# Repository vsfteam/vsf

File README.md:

# VSF -- Versaloon Software Framework

[中文](README_zh.md) |

Full name of VSF is "Versaloon Software Framework". VSF is an open-source software framework for embedded applications based on Apache2 license. VSF includes hal, a pre-emptive multi-thread kernel, services and components. VSF is implemented by C language with object-oriented programming methods(PLOOC).

## Overall Framework

## Catalogue
| Name               | Description                                               |
| ------------------ | --------------------------------------------------------- |
| document           | document                                                  |
| doxygen            | configuration of doxygen                                  |
| example            | demo codes                                                |
| hardware           | hardware of VSF development boards                        |
| patch              | some patches(for 3rd-party components, etc)               |
| script             |                                                           |
|  &emsp;cmake       | cmake scripts                                             |
| source             | source code of VSF                                        |
|  &emsp;component   | component(filesystem, stacks, UI, drivers, etc)           |
|  &emsp;hal         | hardware abstraction layer(ARCH support, chip drivers)    |
|  &emsp;kernel      | VSF pre-emptive/collaborative kernel                      |
|  &emsp;osa_service | software services based on kernel                         |
|  &emsp;service     | software services                                         |
|  &emsp;shell       | shell to use application software for other systems      |
|  &emsp;utilities   | base software utilities(preprocessor, compiler, list, etc)|

## Kernel
Pre-emptive kernel based on event-driven architecture, supporting mcs51, 8bit MCU, 32/64 bit ARM, riscv, x86, etc.

- event-driven architecture, sleep if no event occurred, lower-power naturally
- in pre-emptive mode, task switch is implemented by hardware swi(software interrupt), priority of task is the priority of the swi.
- pre-emptive scheduling for tasks with different priority, collaborative scheduling for tasks with the same priority
- can run in other RTOS as a task, or as swi ISR
- different tasks
  - event handler task -- minimum resources usage, 20 bytes ram usage for minimum configuration, 40 bytes ram usage for normal configuration
  - pt task
  - thread with dedicated stack -- depending on setjmp in libc
  - fsm task
  - other tasks in shell, eg pthread
- IPC: semaphore, mutex, trigger, queue, etc

## Components
- Reasonable framework for code re-use
- declarative development model
- standard interface, standard port for 3rd-party components
- software components
  - distbus -- distributed bus framework
  - fifo
  - heap
  - json
  - pool
  - stream
  - trace
- Components
  - fs -- filesystem with vfs support
  - input -- input sub-system
  - mal -- memory abstraction layer(normally known as 'block' device)
  - scsi -- SCSI device
  - tcpip -- TCPIP stack and netdrv drivers
  - ui -- UI and display drivers
  - usb -- USB host/slave stacks
  - bt -- bt stack(using btstack)

## HAL -- hardware abstraction layer
- standard hal interface and API -- eg: vsf_spi_init can be used with hardware SPI, GPIO emulated SPI, SPI from external usb device, etc
- IP core driver -- simplify porting by implement clock, reset, interrupt functions which is not provided by IP core
- template for different interfaces and functionalities
- interfaces
  - PM
  - GPIO
  - SPI
  - I2C
  - PWM
  - ADC
  - SWI
  - USART
  - FLASH
  - USB
  - ethernet

## Shell
To use applications from other system, shell can be used.

- SDL -- use applications based on SDL directly
- linux -- use applications based on linux directly
  - posix
  - devfs
  - socket
  - console
  - libraries
    - libusb
    - libgen
    - libsdl2
    - libcurl
    - etc

## 3rd-party
| Software          | Path                                                          | License    | Link                                               |
|-------------------|---------------------------------------------------------------|------------|----------------------------------------------------|
| btstack           | source/component/3rd-party/btstack/raw                        | Other      | https://github.com/bluekitchen/btstack             |
| coremark          | source/component/3rd-party/coremark/raw                       | Apache     | https://github.com/eembc/coremark                  |
| freetype          | source/component/3rd-party/freetype/raw                       | FreeType   | https://freetype.org/                              |
| zlib              | source/component/3rd-party/zlib/raw                           | zlib       | http://zlib.net/                                   |
| nuklear           | source/component/3rd-party/nuklear/raw                        | MTI        | https://github.com/Immediate-Mode-UI/Nuklear       |
| nnom              | source/component/3rd-party/nnom/raw                           | Apache 2.0 | https://github.com/majianjia/nnom                  |
| lua               | source/component/3rd-party/lua/raw                            | MIT        | https://www.lua.org/                               |
| lwip              | source/component/3rd-party/lwip/raw                           | BSD        | https://savannah.nongnu.org/projects/lwip/         |
| libpng            | source/component/3rd-party/libpng/raw                         | PNG2       | https://libpng.sf.net                              |
| libjpeg-turbo     | source/component/3rd-party/libjpeg-turbo/raw                  | BSD        | https://libjpeg-turbo.org/                         |
| SDL_ttf           | source/shell/media/sdl2/3rd-party/SDL_ttf                     | zlib       | https://hg.libsdl.org/SDL_ttf/                     |
| SDL_image         | source/shell/media/sdl2/3rd-party/SDL_image                   | zlib       | https://hg.libsdl.org/SDL_image/                   |
| lvgl              | source/component/3rd-party/lvgl/raw/lvgl                      | MIT        | https://lvgl.io/                                   |
| lv_lib_freetype   | source/component/3rd-party/lvgl/extension/lv_lib_freetype/raw | MIT        | https://lvgl.io/                                   |
| CMSIS             | source/utilities/compiler/arm/3rd-party/CMSIS                 | Apache 2.0 | https://github.com/ARM-software/CMSIS_5            |
| PLOOC             | source/utilities/3rd-party/PLOOC/raw                          | Apache 2.0 | https://github.com/GorgonMeducer/PLOOC             |
| mbedtls           | source/component/3rd-party/mbedtls/raw                        | Apache 2.0 | https://tls.mbed.org/                              |
| Segger_RTT        | source/component/3rd-party/segger/raw/RTT                     | segger     | https://wiki.segger.com/RTT                        |
| Segger_SystemView | source/component/3rd-party/segger/raw/SystemView              | segger     | https://wiki.segger.com/SystemView                 |
| nuconsole         | source/component/3rd-party/nuconsole/raw                      | nuvoton    | https://www.nuvoton.com.cn/                        |
| AIC8800M_SDK      | source/hal/driver/AIC/AIC8800/vendor                          | aic        | http://www.aicsemi.com/                            |
| awtk              |                                                               | LGPL 2.1   | https://www.zlg.cn/index/pub/awtk.html             |
| littlefs          | source/component/3rd-party/littlefs/raw                       | BSD        | https://github.com/littlefs-project/littlefs       |
| getopt_long       | source/shell/sys/linux/lib/3rd-party/getopt                   | OpenBSD    | https://github.com/openbsd/src                     |
| regex             | source/shell/sys/linux/lib/3rd-party/regex                    | OpenBSD    | https://github.com/openbsd/src                     |
| fnmatch           | source/shell/sys/linux/lib/3rd-party/fnmatch                  | BSD        | http://www.jbox.dk/sanos/source/lib/fnmatch.c.html |
| glob              | source/shell/sys/linux/lib/3rd-party/glob                     | BSD        | https://github.com/cloudius-systems/musl           |
| setjmp            | source/hal/arch/x86/win                                       | BSD        |                                                    |
| libtuv            | source/shell/sys/linux/lib/3rd-party/libtuv/raw               | Apache 2.0 | https://github.com/Samsung/libtuv                  |
| scgui             | source/component/ui/tgui/view/scgui_view/scgui.c&h            | MIT        | https://gitee.com/li_yucheng/scgui                 |

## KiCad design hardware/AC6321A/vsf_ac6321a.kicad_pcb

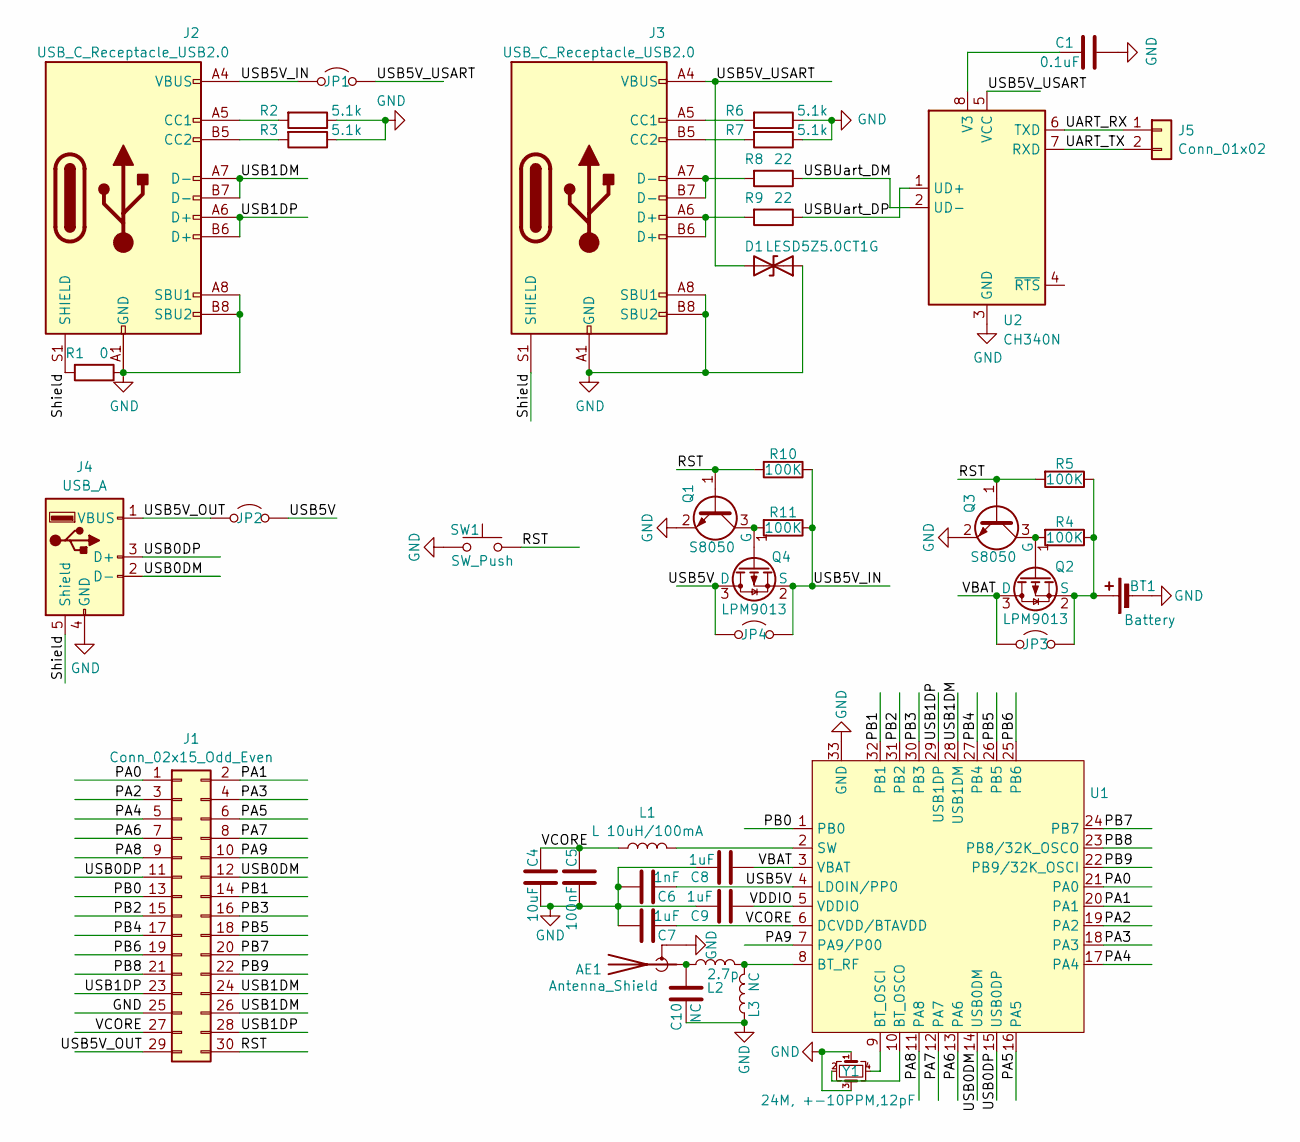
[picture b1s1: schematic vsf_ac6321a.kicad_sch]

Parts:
AE1: Antenna_Shield; Texas_SWRA117D_2.4GHz_Right
BT1: Battery; PinHeader_1x02_P2.54mm_Vertical
C1: 0.1uF; C_0402_1005Metric
C4: 10uF; C_0402_1005Metric
C5: 100nF; C_0402_1005Metric
C6: 1nF; C_0402_1005Metric
C7, C8, C9: 1uF; C_0402_1005Metric
C10: NC; C_0402_1005Metric
D1: LESD5Z5.0CT1G; D_SOD-523
J1: Conn_02x15_Odd_Even; PinHeader_2x15_P2.54mm_Horizontal
J2, J3: USB_C_Receptacle_USB2.0; USB_C_Receptacle_Palconn_UTC16-G_DOWN1.6
J4: USB_A; USB-A-8.5_DOWN3.4
J5: Conn_01x02; PinHeader_1x02_P2.54mm_Vertical
JP1, JP2, JP3, JP4: Jumper_2_Open; SolderJumper-2_P0.8mm_Open_Pad0.6x0.8mm
L1: L 10uH/100mA; L_0603_1608Metric
L2: 2.7p; L_0603_1608Metric
L3: NC; L_0603_1608Metric
Q1, Q3: S8050; TSOT-23
Q2, Q4: LPM9013; SOT-23
R1: 0; R_0402_1005Metric
R2, R3, R6, R7: 5.1k; R_0402_1005Metric
R4, R5, R10, R11: 100K; R_0402_1005Metric
R8, R9: 22; R_0402_1005Metric
SW1: SW_Push; JHA004
U1: QFN-32-1EP_4x4mm_P0.4mm_EP2.65x2.65mm
U2: CH340N; SOP-8_3.9x4.9mm_P1.27mm
Y1: 24M, +-10PPM,12pF; Oscillator_SMD_Abracon_ASE-4Pin_3.2x2.5mm

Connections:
/PA0: J1.1, U1.21 (PA0)
/PA1: J1.2, U1.20 (PA1)
/PA2: J1.3, U1.19 (PA2)
/PA3: J1.4, U1.18 (PA3)
/PA4: J1.5, U1.17 (PA4)
/PA5: J1.6, U1.16 (PA5)
/PA6: J1.7, U1.13 (PA6)
/PA7: J1.8, U1.12 (PA7)
/PA8: J1.9, U1.11 (PA8)
/PA9: J1.10, U1.7 (PA9/P00)
/PB0: J1.13, U1.1 (PB0)
/PB1: J1.14, U1.32 (PB1)
/PB2: J1.15, U1.31 (PB2)
/PB3: J1.16, U1.30 (PB3)
/PB4: J1.17, U1.27 (PB4)
/PB5: J1.18, U1.26 (PB5)
/PB6: J1.19, U1.25 (PB6)
/PB7: J1.20, U1.24 (PB7)
/PB8: J1.21, U1.23 (PB8/32K_OSCO)
/PB9: J1.22, U1.22 (PB9/32K_OSCI)
/RST: J1.30, Q1.1 (B), Q3.1 (B), R5.2, R10.2, SW1.2
/Shield: J2.S1 (SHIELD), J3.S1 (SHIELD), J4.5 (Shield), R1.2
/UART_RX: J5.1, U2.6 (TXD)
/UART_TX: J5.2, U2.7 (RXD)
/USB0DM: J1.12, J4.2 (D-), U1.14 (USB0DM)
/USB0DP: J1.11, J4.3 (D+), U1.15 (USB0DP)
/USB1DM: J1.24, J1.26, J2.A7 (D-), J2.B7 (D-), U1.28 (USB1DM)
/USB1DP: J1.23, J1.28, J2.A6 (D+), J2.B6 (D+), U1.29 (USB1DP)
/USB5V: C6.2, JP2.2 (B), JP4.1 (A), Q4.3 (D), U1.4 (LDOIN/PP0)
/USB5V_IN: J2.A4 (VBUS), J2.A9 (VBUS), J2.B4 (VBUS), J2.B9 (VBUS), JP1.1 (A), JP4.2 (B), Q4.2 (S), R10.1, R11.1
/USB5V_OUT: J1.29, J4.1 (VBUS), JP2.1 (A)
/USB5V_USART: D1.2 (A2), J3.A4 (VBUS), J3.A9 (VBUS), J3.B4 (VBUS), J3.B9 (VBUS), JP1.2 (B), U2.5 (VCC)
/USBUart_DM: R8.1, U2.2 (UD-)
/USBUart_DP: R9.1, U2.1 (UD+)
/VBAT: C8.2, JP3.1 (A), Q2.3 (D), U1.3 (VBAT)
/VCORE: C4.2, C5.2, C7.2, J1.27, L1.1, U1.6 (DCVDD/BTAVDD)
/VDDIO: C9.2, U1.5 (VDDIO)
GND: AE1.2 (Shield), BT1.2 (-), C1.2, C4.1, C5.1, C6.1, C7.1, C8.1, C9.1, C10.1, D1.1 (A1), J1.25, J2.A1 (GND), J2.A8 (SBU1), J2.A12 (GND), J2.B1 (GND), J2.B8 (SBU2), J2.B12 (GND), J3.A1 (GND), J3.A8 (SBU1), J3.A12 (GND), J3.B1 (GND), J3.B8 (SBU2), J3.B12 (GND), J4.4 (GND), L3.1, Q1.2 (E), Q3.2 (E), R1.1, R2.1, R3.1, R6.1, R7.1, SW1.1, U1.33 (GND), U2.3 (GND), Y1.1, Y1.3
unnamed: AE1.1 (A), C10.2, L2.1
unnamed: BT1.1 (+), JP3.2 (B), Q2.2 (S), R4.1, R5.1
unnamed: J2.A5 (CC1), R2.2
unnamed: J2.B5 (CC2), R3.2
unnamed: J3.A5 (CC1), R6.2
unnamed: J3.B5 (CC2), R7.2
unnamed: J3.A6 (D+), J3.B6 (D+), R9.2
unnamed: J3.A7 (D-), J3.B7 (D-), R8.2
unnamed: Q1.3 (C), Q4.1 (G), R11.2
unnamed: Q2.1 (G), Q3.3 (C), R4.2
unnamed: U1.9 (BT_OSCI), Y1.4
unnamed: U1.10 (BT_OSCO), Y1.2
unnamed: L2.2, L3.2, U1.8 (BT_RF)
unnamed: L1.2, U1.2 (SW)
unnamed: C1.1, U2.8 (V3)

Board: 2 copper layers, 42 parts (0 on the bottom side), 53 nets, no tracks yet.

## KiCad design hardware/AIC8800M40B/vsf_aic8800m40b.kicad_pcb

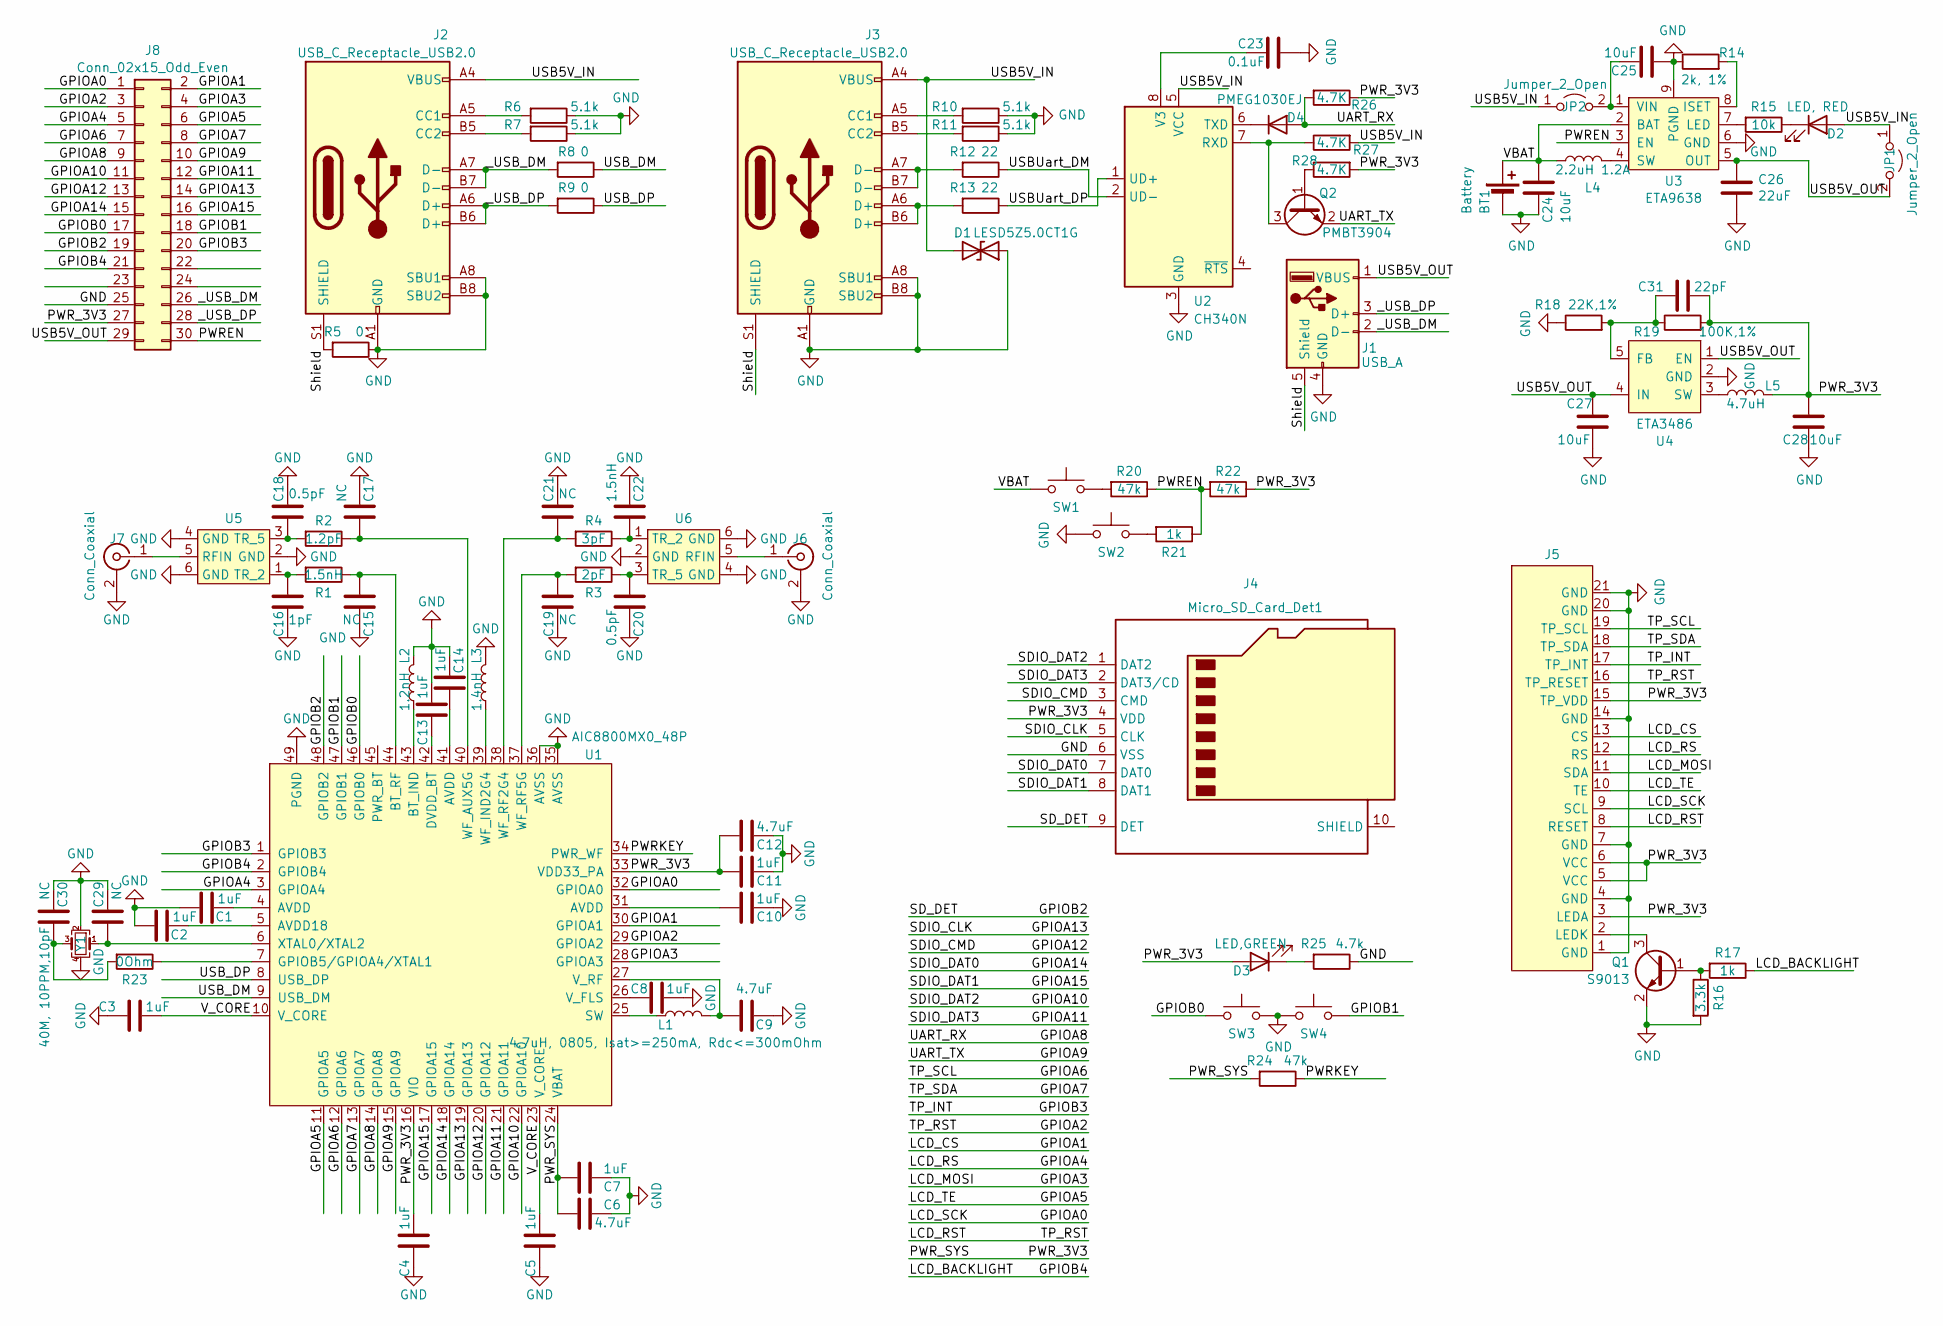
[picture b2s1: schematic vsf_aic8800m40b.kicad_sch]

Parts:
BT1: Battery; PinHeader_1x02_P2.54mm_Vertical
C1, C2, C3, C4, C5, C7, C8, C10, C11, C13, C14: 1uF; C_0402_1005Metric
C6, C9, C12: 4.7uF; C_0402_1005Metric
C15, C17, C19, C21, C29, C30: NC; C_0402_1005Metric
C16: 1pF; C_0402_1005Metric
C18, C20: 0.5pF; C_0402_1005Metric
C22: 1.5nH; C_0402_1005Metric
C23: 0.1uF; C_0402_1005Metric
C24, C25: 10uF; C_1206_3216Metric
C26: 22uF; C_1206_3216Metric
C27, C28: 10uF; C_0805_2012Metric
C31: 22pF; C_0402_1005Metric
D1: LESD5Z5.0CT1G; D_SOD-523
D2: LED, RED; LED_0603_1608Metric
D3: LED,GREEN; LED_0603_1608Metric
D4: PMEG1030EJ; D_SOD-323
J1: USB_A; USB-A-8.5_DOWN3.4
J2, J3: USB_C_Receptacle_USB2.0; USB_C_Receptacle_Palconn_UTC16-G_DOWN1.6
J4: Micro_SD_Card_Det1; MicroSD_Tiny
J5: Molex_502250-2191_2Rows-21Pins-1MP_P0.60mm_Horizontal
J6, J7: Conn_Coaxial; U.FL_Molex_MCRF_73412-0110_Vertical
J8: Conn_02x15_Odd_Even; PinHeader_2x15_P2.54mm_Horizontal
JP1, JP2: Jumper_2_Open; SolderJumper-2_P0.8mm_Open_Pad0.6x0.8mm
L1: 4.7uH, 0805, Isat>=250mA, Rdc<=300mOhm; L_0805_2012Metric
L2: 1.2nH; L_0402_1005Metric
L3: 1.4nH; L_0402_1005Metric
L4: 2.2uH 1.2A; L_1210_3225Metric
L5: 4.7uH; L_1210_3225Metric
Q1: S9013; SOT-23
Q2: PMBT3904; SOT-23
R1: 1.5nH; R_0402_1005Metric
R2: 1.2pF; R_0402_1005Metric
R3: 2pF; R_0402_1005Metric
R4: 3pF; R_0402_1005Metric
R5, R8, R9: 0; R_0402_1005Metric
R6, R7, R10, R11: 5.1k; R_0402_1005Metric
R12, R13: 22; R_0402_1005Metric
R14: 2k, 1%; R_0402_1005Metric
R15: 10k; R_0402_1005Metric
R16: 3.3k; R_0402_1005Metric
R17, R21: 1k; R_0402_1005Metric
R18: 22K,1%; R_0402_1005Metric
R19: 100K,1%; R_0402_1005Metric
R20, R22, R24: 47k; R_0402_1005Metric
R23: 0Ohm; R_0402_1005Metric
R25: 4.7k; R_0402_1005Metric
R26, R27, R28: 4.7K; R_0402_1005Metric
SW1, SW2, SW3, SW4: SW_Push; JHA004
U1: AIC8800MX0_48P; QFN-48.10.14.10.14-1EP_5x5mm_P0.35mm_EP3.7x3.7mm_ThermalVias
U2: CH340N; SOP-8_3.9x4.9mm_P1.27mm
U3: ETA9638; HSOP-8-1EP_3.9x4.9mm_P1.27mm_EP2.41x3.1mm_ThermalVias
U4: ETA3486; SOT-23-5
U5, U6: Filter_SLFD18-5R950G-07T
Y1: 40M, 10PPM,10pF; Oscillator_SMD_Abracon_ASE-4Pin_3.2x2.5mm

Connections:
/GPIOA0: J5.9 (SCL), J8.1, U1.32 (GPIOA0)
/GPIOA1: J5.13 (CS), J8.2, U1.30 (GPIOA1)
/GPIOA2: J5.8 (RESET), J5.16 (TP_RESET), J8.3, U1.29 (GPIOA2)
/GPIOA3: J5.11 (SDA), J8.4, U1.28 (GPIOA3)
/GPIOA4: J5.12 (RS), J8.5, U1.3 (GPIOA4)
/GPIOA5: J5.10 (TE), J8.6, U1.11 (GPIOA5)
/GPIOA6: J5.19 (TP_SCL), J8.7, U1.12 (GPIOA6)
/GPIOA7: J5.18 (TP_SDA), J8.8, U1.13 (GPIOA7)
/GPIOA8: D4.2 (A), J8.9, R26.2, U1.14 (GPIOA8)
/GPIOA9: J8.10, Q2.2 (E), U1.15 (GPIOA9)
/GPIOA10: J4.1 (DAT2), J8.11, U1.22 (GPIOA10)
/GPIOA11: J4.2 (DAT3/CD), J8.12, U1.21 (GPIOA11)
/GPIOA12: J4.3 (CMD), J8.13, U1.20 (GPIOA12)
/GPIOA13: J4.5 (CLK), J8.14, U1.19 (GPIOA13)
/GPIOA14: J4.7 (DAT0), J8.15, U1.18 (GPIOA14)
/GPIOA15: J4.8 (DAT1), J8.16, U1.17 (GPIOA15)
/GPIOB0: J8.17, SW3.1, U1.46 (GPIOB0)
/GPIOB1: J8.18, SW4.2, U1.47 (GPIOB1)
/GPIOB2: J4.9 (DET), J8.19, U1.48 (GPIOB2)
/GPIOB3: J5.17 (TP_INT), J8.20, U1.1 (GPIOB3)
/GPIOB4: J8.21, R17.1, U1.2 (GPIOB4)
/PWREN: J8.30, R20.1, R21.1, R22.2, U3.3 (EN)
/PWRKEY: R24.1, U1.34 (PWR_WF)
/PWR_3V3: C4.1, C6.1, C7.1, C11.1, C12.1, C28.1, C31.2, D3.2 (A), J4.4 (VDD), J5.3 (LEDA), J5.5 (VCC), J5.6 (VCC), J5.15 (TP_VDD), J8.27, L5.2, R19.2, R22.1, R24.2, R26.1, R28.2, U1.16 (VIO), U1.24 (VBAT), U1.33 (VDD33_PA)
/Shield: J1.5 (Shield), J2.S1 (SHIELD), J3.S1 (SHIELD), R5.2
/USB5V_IN: D1.2 (A2), D2.2 (A), J2.A4 (VBUS), J2.A9 (VBUS), J2.B4 (VBUS), J2.B9 (VBUS), J3.A4 (VBUS), J3.A9 (VBUS), J3.B4 (VBUS), J3.B9 (VBUS), JP1.1 (A), JP2.1 (A), R27.2, U2.5 (VCC)
/USB5V_OUT: C26.1, C27.1, J1.1 (VBUS), J8.29, JP1.2 (B), U3.5 (OUT), U4.1 (EN), U4.4 (IN)
/USBUart_DM: R12.1, U2.2 (UD-)
/USBUart_DP: R13.1, U2.1 (UD+)
/USB_DM: R8.1, U1.9 (USB_DM)
/USB_DP: R9.1, U1.8 (USB_DP)
/VBAT: BT1.1 (+), C24.1, L4.1, SW1.1, U3.2 (BAT)
/V_CORE: C3.1, C5.1, U1.10 (V_CORE), U1.23 (V_CORE)
/_USB_DM: J1.2 (D-), J2.A7 (D-), J2.B7 (D-), J8.26, R8.2
/_USB_DP: J1.3 (D+), J2.A6 (D+), J2.B6 (D+), J8.28, R9.2
GND: BT1.2 (-), C1.2, C2.2, C3.2, C4.2, C5.2, C6.2, C7.2, C8.2, C9.1, C10.2, C11.2, C12.2, C13.1, C14.1, C15.2, C16.2, C17.1, C18.1, C19.2, C20.2, C21.1, C22.1, C23.2, C24.2, C25.2, C26.2, C27.2, C28.2, C29.1, C30.1, D1.1 (A1), J1.4 (GND), J2.A1 (GND), J2.A8 (SBU1), J2.A12 (GND), J2.B1 (GND), J2.B8 (SBU2), J2.B12 (GND), J3.A1 (GND), J3.A8 (SBU1), J3.A12 (GND), J3.B1 (GND), J3.B8 (SBU2), J3.B12 (GND), J4.6 (VSS), J5.1 (GND), J5.4 (GND), J5.7 (GND), J5.14 (GND), J5.20 (GND), J5.21 (GND), J6.2 (Ext), J7.2 (Ext), J8.25, L2.2, L3.2, Q1.2 (E), R5.1, R6.1, R7.1, R10.1, R11.1, R14.1, R16.2, R18.1, R25.1, SW2.1, SW3.2, SW4.1, U1.35 (AVSS), U1.36 (AVSS), U1.49 (PGND), U2.3 (GND), U3.6 (GND), U3.9 (PGND), U4.2 (GND), U5.2 (GND), U5.4 (GND), U5.6 (GND), U6.2 (GND), U6.4 (GND), U6.6 (GND), Y1.2, Y1.4
unnamed: C1.1, U1.4 (AVDD)
unnamed: C10.1, U1.31 (AVDD)
unnamed: C14.2, U1.41 (AVDD)
unnamed: C30.2, R23.2, Y1.3
unnamed: D2.1 (K), R15.1
unnamed: D3.1 (K), R25.2
unnamed: D4.1 (K), U2.6 (TXD)
unnamed: J2.A5 (CC1), R6.2
unnamed: J2.B5 (CC2), R7.2
unnamed: J3.A5 (CC1), R10.2
unnamed: J3.B5 (CC2), R11.2
unnamed: J3.A6 (D+), J3.B6 (D+), R13.2
unnamed: J3.A7 (D-), J3.B7 (D-), R12.2
unnamed: J5.2 (LEDK), Q1.3 (C)
unnamed: J6.1 (In), U6.5 (RFIN)
unnamed: J7.1 (In), U5.5 (RFIN)
unnamed: C25.1, JP2.2 (B), U3.1 (VIN)
unnamed: Q1.1 (B), R16.1, R17.2
unnamed: Q2.1 (B), R28.1
unnamed: Q2.3 (C), R27.1, U2.7 (RXD)
unnamed: R20.2, SW1.2
unnamed: R21.2, SW2.2
unnamed: C2.1, U1.5 (AVDD18)
unnamed: L2.1, U1.43 (BT_IND)
unnamed: C15.1, R1.1, U1.44 (BT_RF)
unnamed: C13.2, U1.42 (DVDD_BT)
unnamed: R23.1, U1.7 (GPIOB5/GPIOA4/XTAL1)
unnamed: L1.1, U1.25 (SW)
unnamed: C8.1, U1.26 (V_FLS)
unnamed: C9.2, L1.2, U1.27 (V_RF)
unnamed: C17.2, R2.1, U1.40 (WF_AUX5G)
unnamed: L3.1, U1.39 (WF_IND2G4)
unnamed: C21.2, R4.2, U1.38 (WF_RF2G4)
unnamed: C19.1, R3.2, U1.37 (WF_RF5G)
unnamed: C29.2, U1.6 (XTAL0/XTAL2), Y1.1
unnamed: C23.1, U2.8 (V3)
unnamed: R14.2, U3.8 (ISET)
unnamed: R15.2, U3.7 (LED)
unnamed: L4.2, U3.4 (SW)
unnamed: C31.1, R18.2, R19.1, U4.5 (FB)
unnamed: L5.1, U4.3 (SW)
unnamed: C16.1, R1.2, U5.1 (TR_2)
unnamed: C18.2, R2.2, U5.3 (TR_5)
unnamed: C22.2, R4.1, U6.1 (TR_2)
unnamed: C20.1, R3.1, U6.3 (TR_5)

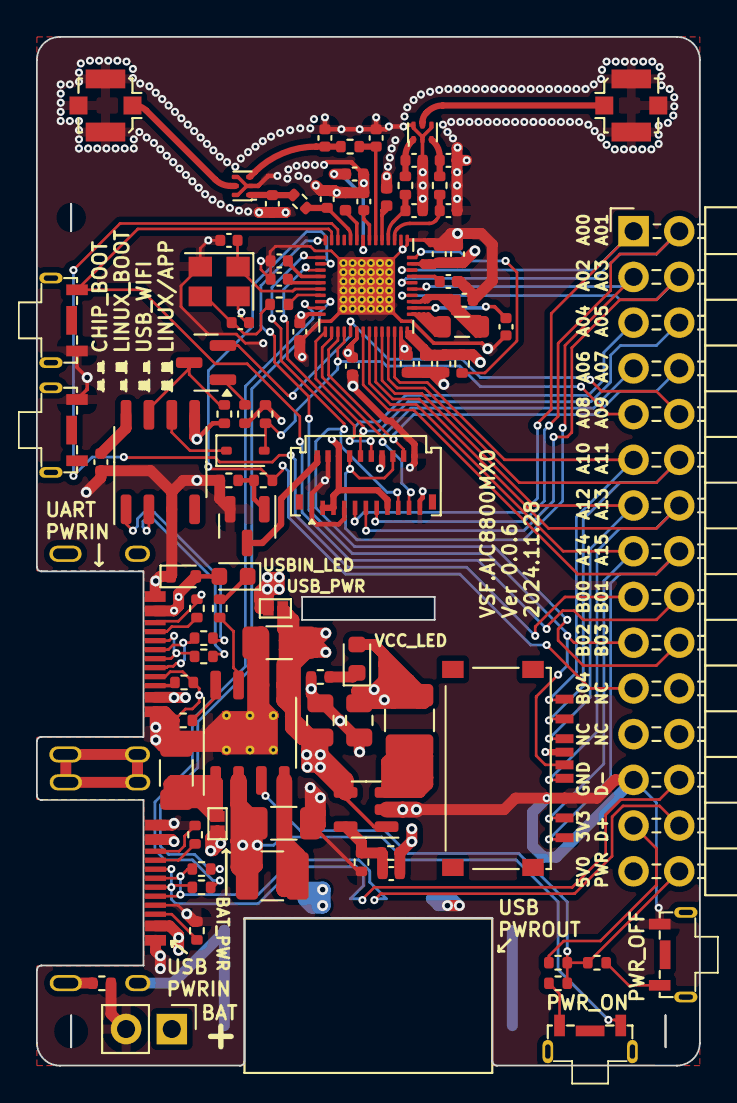
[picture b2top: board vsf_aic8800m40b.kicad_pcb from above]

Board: 4 copper layers, 36.8 x 57.2 mm, 92 parts (0 on the bottom side), 81 nets.

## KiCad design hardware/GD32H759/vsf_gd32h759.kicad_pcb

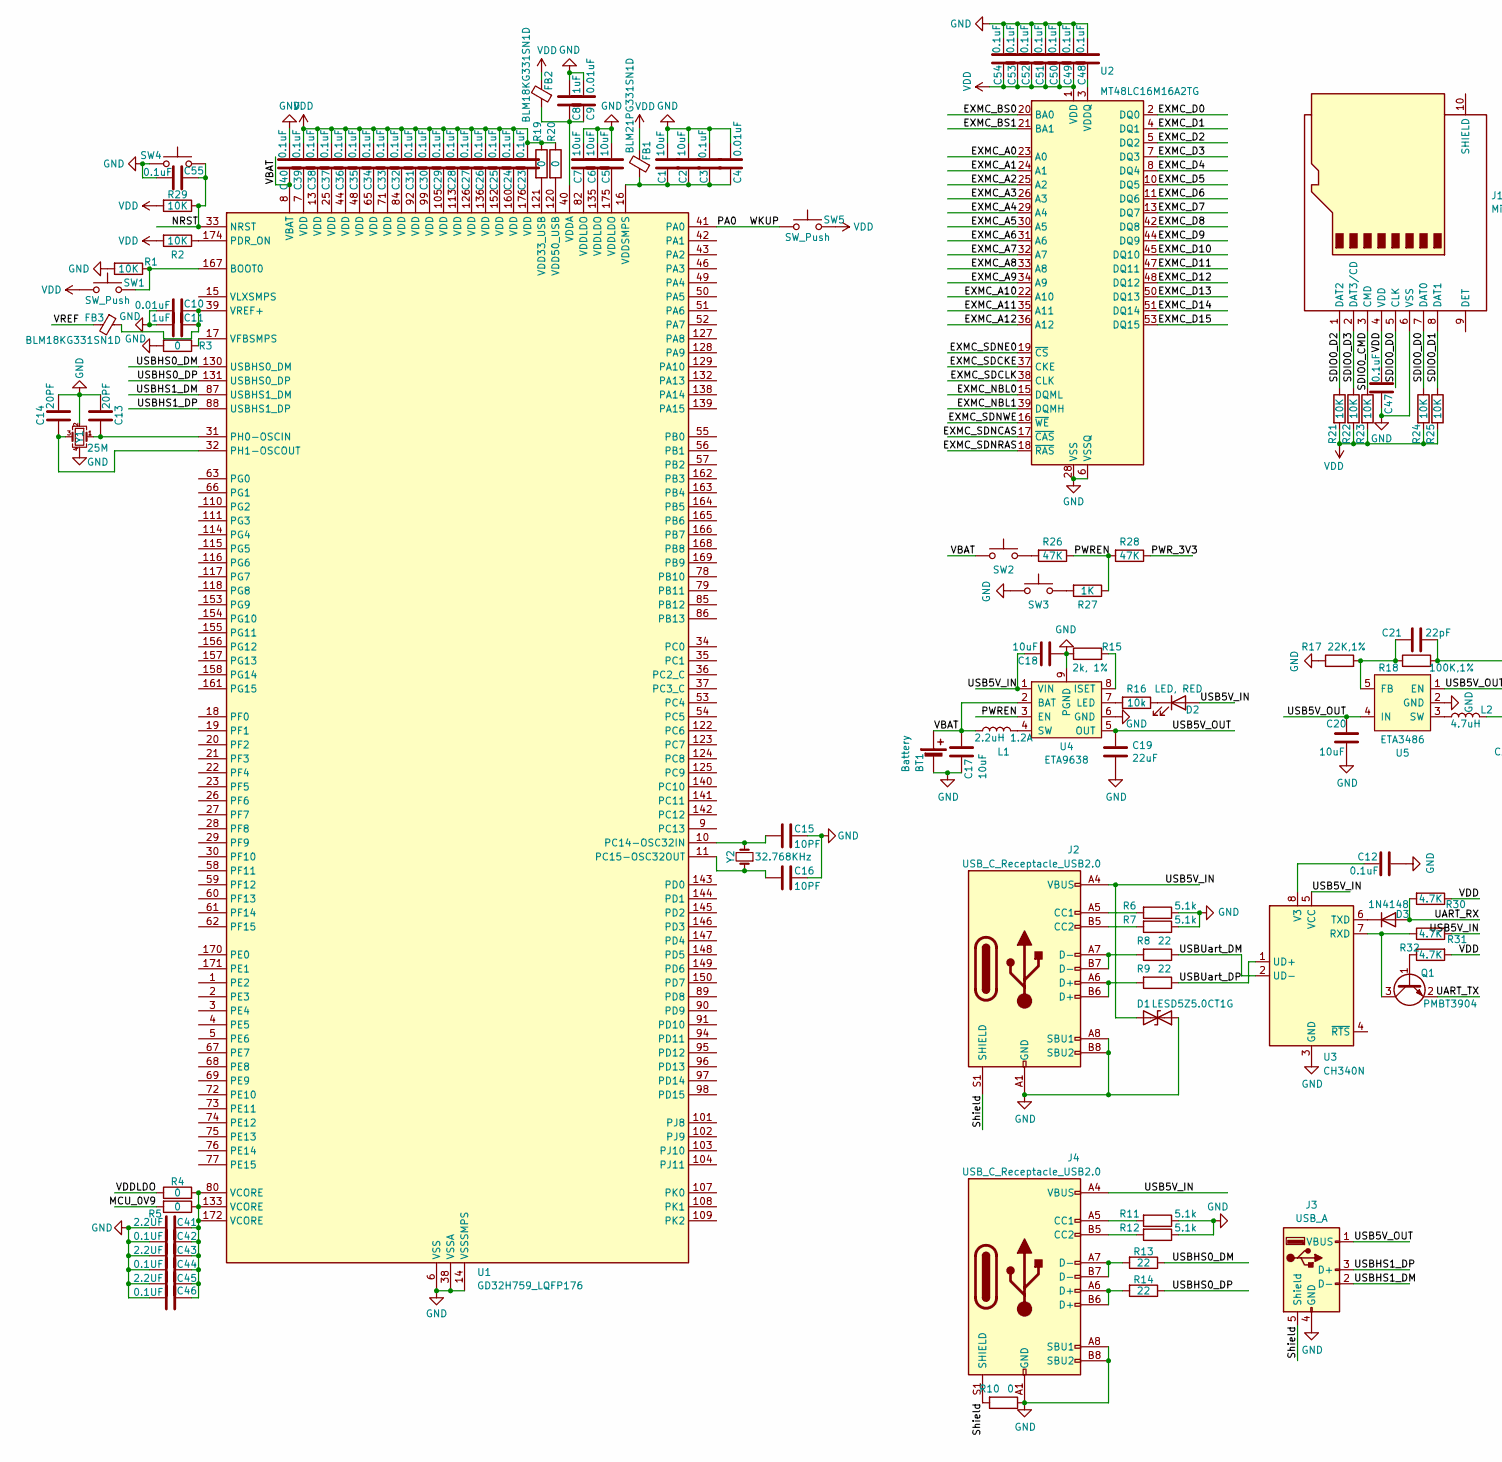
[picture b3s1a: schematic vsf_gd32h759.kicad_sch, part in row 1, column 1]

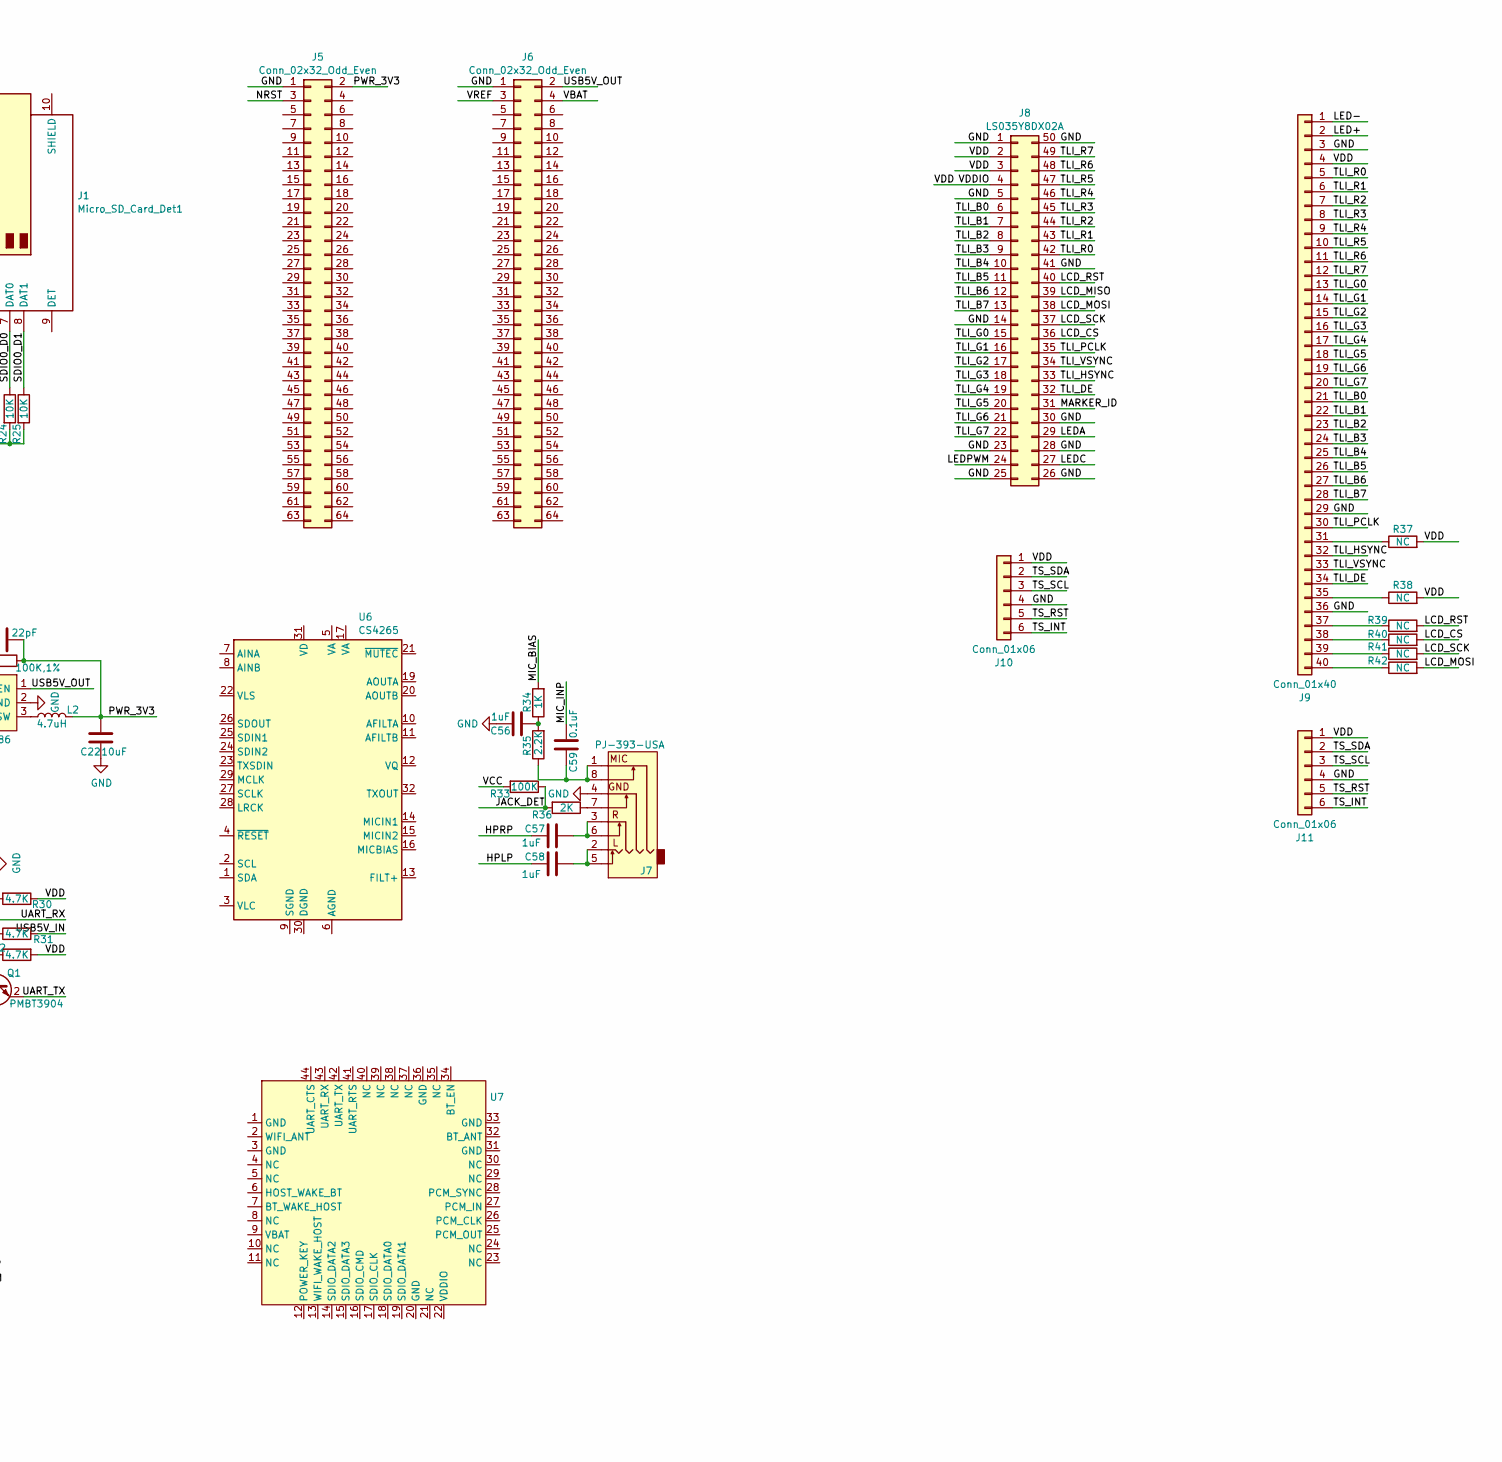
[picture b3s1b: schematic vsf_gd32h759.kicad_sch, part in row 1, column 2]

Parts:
BT1: Battery; PinHeader_1x02_P2.54mm_Vertical
C1, C2, C5, C6, C7: 10uF; C_0402_1005Metric
C3, C12, C23, C24, C25, C26, C27, C28, C29, C30, C31, C32, C33, C34, C35, C36, C37, C38, C39, C40, C47, C48, C49, C50, C51, C52, C53, C54, C55, C59: 0.1uF; C_0402_1005Metric
C4, C9, C10: 0.01uF; C_0402_1005Metric
C8, C11, C56, C57, C58: 1uF; C_0402_1005Metric
C13, C14: 20PF; C_0402_1005Metric
C15, C16: 10PF; C_0402_1005Metric
C17, C18: 10uF; C_1206_3216Metric
C19: 22uF; C_1206_3216Metric
C20, C22: 10uF; C_0805_2012Metric
C21: 22pF; C_0402_1005Metric
C41, C43, C45: 2.2UF; C_0402_1005Metric
C42, C44, C46: 0.1UF; C_0402_1005Metric
D1: LESD5Z5.0CT1G; D_SOD-523
D2: LED, RED; LED_0603_1608Metric
D3: 1N4148; D_SOD-523
FB1: BLM21PG331SN1D
FB2, FB3: BLM18KG331SN1D
J1: Micro_SD_Card_Det1
J2, J4: USB_C_Receptacle_USB2.0; USB_C_Receptacle_Palconn_UTC16-G_DOWN1.6
J3: USB_A; USB-A-8.5_DOWN3.4
J5, J6: Conn_02x32_Odd_Even; PinHeader_2x32_P2.54mm_Vertical
J7: PJ-393-USA; PJ-393
J8: LS035Y8DX02A
J9: Conn_01x40
J10, J11: Conn_01x06
L1: 2.2uH 1.2A; L_1210_3225Metric
L2: 4.7uH; L_1210_3225Metric
Q1: PMBT3904; SOT-23
R1, R2, R21, R22, R23, R24, R25, R29: 10K; R_0402_1005Metric
R3, R4, R5, R10, R19, R20: 0; R_0402_1005Metric
R6, R7, R11, R12: 5.1k; R_0402_1005Metric
R8, R9, R13, R14: 22; R_0402_1005Metric
R15: 2k, 1%; R_0402_1005Metric
R16: 10k; R_0402_1005Metric
R17: 22K,1%; R_0402_1005Metric
R18: 100K,1%; R_0402_1005Metric
R26, R28: 47K; R_0402_1005Metric
R27, R34: 1K; R_0402_1005Metric
R30, R31, R32: 4.7K; R_0402_1005Metric
R33: 100K; R_0402_1005Metric
R35: 2.2K; R_0402_1005Metric
R36: 2K; R_0402_1005Metric
R37, R38, R39, R40, R41, R42: NC; R_0402_1005Metric
SW1, SW2, SW3: SW_Push; JHA004
SW4, SW5: SW_Push; Key_2Pin_2.9X4.3
U1: GD32H759_LQFP176; LQFP-176_24x24mm_P0.5mm
U2: MT48LC16M16A2TG; TSOP-II-54_22.2x10.16mm_P0.8mm
U3: CH340N; SOP-8_3.9x4.9mm_P1.27mm
U4: ETA9638; HSOP-8-1EP_3.9x4.9mm_P1.27mm_EP2.41x3.1mm_ThermalVias
U5: ETA3486; SOT-23-5
U6: CS4265; QFN-32-1EP_5x5mm_P0.5mm_EP3.6x3.6mm
U7: (no value)
Y1: 25M; Oscillator_SMD_Abracon_ASE-4Pin_3.2x2.5mm
Y2: 32.768KHz

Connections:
/EXMC_A0: U2.23 (A0)
/EXMC_A1: U2.24 (A1)
/EXMC_A2: U2.25 (A2)
/EXMC_A3: U2.26 (A3)
/EXMC_A4: U2.29 (A4)
/EXMC_A5: U2.30 (A5)
/EXMC_A6: U2.31 (A6)
/EXMC_A7: U2.32 (A7)
/EXMC_A8: U2.33 (A8)
/EXMC_A9: U2.34 (A9)
/EXMC_A10: U2.22 (A10)
/EXMC_A11: U2.35 (A11)
/EXMC_A12: U2.36 (A12)
/EXMC_BS0: U2.20 (BA0)
/EXMC_BS1: U2.21 (BA1)
/EXMC_D0: U2.2 (DQ0)
/EXMC_D1: U2.4 (DQ1)
/EXMC_D2: U2.5 (DQ2)
/EXMC_D3: U2.7 (DQ3)
/EXMC_D4: U2.8 (DQ4)
/EXMC_D5: U2.10 (DQ5)
/EXMC_D6: U2.11 (DQ6)
/EXMC_D7: U2.13 (DQ7)
/EXMC_D8: U2.42 (DQ8)
/EXMC_D9: U2.44 (DQ9)
/EXMC_D10: U2.45 (DQ10)
/EXMC_D11: U2.47 (DQ11)
/EXMC_D12: U2.48 (DQ12)
/EXMC_D13: U2.50 (DQ13)
/EXMC_D14: U2.51 (DQ14)
/EXMC_D15: U2.53 (DQ15)
/EXMC_NBL0: U2.15 (DQML)
/EXMC_NBL1: U2.39 (DQMH)
/EXMC_SDCKE: U2.37 (CKE)
/EXMC_SDCLK: U2.38 (CLK)
/EXMC_SDNCAS: U2.17 (~CAS)
/EXMC_SDNE0: U2.19 (~CS)
/EXMC_SDNRAS: U2.18 (~RAS)
/EXMC_SDNWE: U2.16 (~WE)
/HPLP: C58.1
/HPRP: C57.1
/JACK_DET: R33.1, R36.2
/LCD_CS: J8.36, R40.2
/LCD_MOSI: J8.38, R42.2
/LCD_RST: J8.40, R39.2
/LCD_SCK: J8.37, R41.2
/MCU_0V9: R5.2
/MIC_BIAS: R34.2
/MIC_INP: C59.1
/NRST: C55.2, J5.3, R29.1, SW4.2, U1.33 (NRST)
/PA0: SW5.1, U1.41 (PA0)
/PWREN: R26.1, R27.1, R28.2, U4.3 (EN)
/PWR_3V3: C21.2, C22.1, J5.2, L2.2, R18.2, R28.1
/SDIO0_CMD: J1.3 (CMD), R23.1
/SDIO0_D0: J1.5 (CLK), J1.7 (DAT0), R24.1
/SDIO0_D1: J1.8 (DAT1), R25.1
/SDIO0_D2: J1.1 (DAT2), R21.1
/SDIO0_D3: J1.2 (DAT3/CD), R22.1
/Shield: J2.S1 (SHIELD), J3.5 (Shield), J4.S1 (SHIELD), R10.2
/UART_RX: D3.2 (A), R30.2
/UART_TX: Q1.2 (E)
/USB5V_IN: C18.1, D1.2 (A2), D2.2 (A), J2.A4 (VBUS), J2.A9 (VBUS), J2.B4 (VBUS), J2.B9 (VBUS), J4.A4 (VBUS), J4.A9 (VBUS), J4.B4 (VBUS), J4.B9 (VBUS), R31.2, U3.5 (VCC), U4.1 (VIN)
/USB5V_OUT: C19.1, C20.1, J3.1 (VBUS), J6.2, U4.5 (OUT), U5.1 (EN), U5.4 (IN)
/USBHS0_DM: R13.1, U1.130 (USBHS0_DM)
/USBHS0_DP: R14.1, U1.131 (USBHS0_DP)
/USBHS1_DM: J3.2 (D-), U1.87 (USBHS1_DM)
/USBHS1_DP: J3.3 (D+), U1.88 (USBHS1_DP)
/USBUart_DM: R8.1, U3.2 (UD-)
/USBUart_DP: R9.1, U3.1 (UD+)
/VBAT: BT1.1 (+), C17.1, C40.2, J6.4, L1.1, SW2.1, U1.8 (VBAT), U4.2 (BAT)
/VCC: R33.2
/VDDLDO: R4.1
/VREF: FB3.2, J6.3
GND: BT1.2 (-), C1.1, C2.1, C3.1, C4.1, C5.1, C6.1, C7.1, C8.1, C9.1, C10.1, C11.1, C12.2, C13.1, C14.1, C15.2, C16.2, C17.2, C18.2, C19.2, C20.2, C22.2, C40.1, C41.1, C42.1, C43.1, C44.1, C45.1, C46.1, C47.2, C48.1, C49.1, C50.1, C51.1, C52.1, C53.1, C54.1, C55.1, C56.1, D1.1 (A1), J1.6 (VSS), J2.A1 (GND), J2.A8 (SBU1), J2.A12 (GND), J2.B1 (GND), J2.B8 (SBU2), J2.B12 (GND), J3.4 (GND), J4.A1 (GND), J4.A8 (SBU1), J4.A12 (GND), J4.B1 (GND), J4.B8 (SBU2), J4.B12 (GND), J5.1, J6.1, J7.4, J8.1, J8.5, J8.14, J8.23, J8.25, J8.26, J8.28, J8.30, J8.41, J8.50, J9.3, J9.29, J9.36, J10.4, J11.4, R1.2, R3.2, R6.1, R7.1, R10.1, R11.1, R12.1, R15.1, R17.1, SW3.1, SW4.1, U1.6 (VSS), U1.12 (VSS), U1.14 (VSSSMPS), U1.24 (VSS), U1.38 (VSSA), U1.45 (VSS), U1.47 (VSS), U1.64 (VSS), U1.70 (VSS), U1.81 (VSS), U1.83 (VSS), U1.93 (VSS), U1.100 (VSS), U1.106 (VSS), U1.112 (VSS), U1.119 (VSS), U1.134 (VSS), U1.137 (VSS), U1.151 (VSS), U1.159 (VSS), U1.173 (VSS), U2.6 (VSSQ), U2.12 (VSSQ), U2.28 (VSS), U2.41 (VSS), U2.46 (VSSQ), U2.52 (VSSQ), U2.54 (VSS), U3.3 (GND), U4.6 (GND), U4.9 (PGND), U5.2 (GND), Y1.2, Y1.4
unnamed: C5.2, U1.175 (VDDLDO)
unnamed: C6.2, U1.135 (VDDLDO)
unnamed: C7.2, U1.82 (VDDLDO)
unnamed: C23.2, U1.176 (VDD)
unnamed: C24.2, U1.160 (VDD)
unnamed: C25.2, U1.152 (VDD)
unnamed: C26.2, U1.136 (VDD)
unnamed: C27.2, U1.126 (VDD)
unnamed: C28.2, U1.113 (VDD)
unnamed: C29.2, U1.105 (VDD)
unnamed: C30.2, U1.99 (VDD)
unnamed: C31.2, U1.92 (VDD)
unnamed: C32.2, U1.84 (VDD)
unnamed: C33.2, U1.71 (VDD)
unnamed: C34.2, U1.65 (VDD)
unnamed: C35.2, U1.48 (VDD)
unnamed: C36.2, U1.44 (VDD)
unnamed: C37.2, U1.25 (VDD)
unnamed: C38.2, U1.13 (VDD)
unnamed: C39.2, U1.7 (VDD)
unnamed: C41.2, C42.2, C43.2, C44.2, C45.2, C46.2, R4.2, R5.1, U1.80 (VCORE), U1.133 (VCORE), U1.172 (VCORE)
unnamed: C48.2, U2.3 (VDDQ), U2.9 (VDDQ), U2.43 (VDDQ), U2.49 (VDDQ)
unnamed: C56.2, R34.1, R35.2
unnamed: C57.2, J7.3, J7.6
unnamed: C58.2, J7.2, J7.5
unnamed: C59.2, J7.1, J7.8, R35.1
unnamed: D2.1 (K), R16.1
unnamed: D3.1 (K), U3.6 (TXD)
unnamed: J2.A5 (CC1), R6.2
unnamed: J2.B5 (CC2), R7.2
unnamed: J2.A6 (D+), J2.B6 (D+), R9.2
unnamed: J2.A7 (D-), J2.B7 (D-), R8.2
unnamed: J4.A5 (CC1), R11.2
unnamed: J4.B5 (CC2), R12.2
unnamed: J4.A6 (D+), J4.B6 (D+), R14.2
unnamed: J4.A7 (D-), J4.B7 (D-), R13.2
unnamed: J7.7, R36.1
unnamed: J8.6, J9.21
unnamed: J8.7, J9.22
unnamed: J8.8, J9.23
unnamed: J8.9, J9.24
unnamed: J8.10, J9.25
unnamed: J8.11, J9.26
unnamed: J8.12, J9.27
unnamed: J8.13, J9.28
unnamed: J8.15, J9.13
unnamed: J8.16, J9.14
unnamed: J8.17, J9.15
unnamed: J8.18, J9.16
unnamed: J8.19, J9.17
unnamed: J8.20, J9.18
unnamed: J8.21, J9.19
unnamed: J8.22, J9.20
unnamed: J8.32, J9.34
unnamed: J8.33, J9.32
unnamed: J8.34, J9.33
unnamed: J8.35, J9.30
unnamed: J8.42, J9.5
unnamed: J8.43, J9.6
unnamed: J8.44, J9.7
unnamed: J8.45, J9.8
unnamed: J8.46, J9.9
unnamed: J8.47, J9.10
unnamed: J8.48, J9.11
unnamed: J8.49, J9.12
unnamed: J9.31, R37.1
unnamed: J9.35, R38.1
unnamed: J9.37, R39.1
unnamed: J9.38, R40.1
unnamed: J9.39, R41.1
unnamed: J9.40, R42.1
unnamed: J10.2, J11.2
unnamed: J10.3, J11.3
unnamed: J10.5, J11.5
unnamed: J10.6, J11.6
unnamed: Q1.1 (B), R32.1
unnamed: Q1.3 (C), R31.1, U3.7 (RXD)
unnamed: R26.2, SW2.2
unnamed: R27.2, SW3.2
unnamed: R1.1, SW1.2, U1.167 (BOOT0)
unnamed: C15.1, U1.10 (PC14-OSC32IN), Y2.2
unnamed: C16.1, U1.11 (PC15-OSC32OUT), Y2.1
unnamed: R2.1, U1.174 (PDR_ON)
unnamed: C13.2, U1.31 (PH0-OSCIN), Y1.1
unnamed: C14.2, U1.32 (PH1-OSCOUT), Y1.3
unnamed: R19.2, U1.121 (VDD33_USB)
unnamed: R20.2, U1.120 (VDD50_USB)
unnamed: C8.2, C9.2, FB2.1, U1.40 (VDDA)
unnamed: C1.2, C2.2, C3.2, C4.2, FB1.1, U1.16 (VDDSMPS)
unnamed: R3.1, U1.17 (VFBSMPS)
unnamed: C10.2, C11.2, FB3.1, U1.39 (VREF+)
unnamed: C12.1, U3.8 (V3)
unnamed: R15.2, U4.8 (ISET)
unnamed: R16.2, U4.7 (LED)
unnamed: L1.2, U4.4 (SW)
unnamed: C21.1, R17.2, R18.1, U5.5 (FB)
unnamed: L2.1, U5.3 (SW)
unnamed: U6.6 (AGND), U6.18 (AGND), U6.33 (AGND)
VDD: C23.1, C24.1, C25.1, C26.1, C27.1, C28.1, C29.1, C30.1, C31.1, C32.1, C33.1, C34.1, C35.1, C36.1, C37.1, C38.1, C39.1, C47.1, C49.2, C50.2, C51.2, C52.2, C53.2, C54.2, FB1.2, FB2.2, J1.4 (VDD), J8.2, J8.3, J8.4, J9.4, J10.1, J11.1, R2.2, R19.1, R20.1, R21.2, R22.2, R23.2, R24.2, R25.2, R29.2, R30.1, R32.2, R37.2, R38.2, SW1.1, SW5.2, U2.1 (VDD), U2.14 (VDD), U2.27 (VDD)

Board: 2 copper layers, 127 parts (0 on the bottom side), 83 nets, no tracks yet.
